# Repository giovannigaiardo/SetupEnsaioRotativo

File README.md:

# SetupEnsaioRotativo
Automação processo de ensaio rotativo para laboratório de plugs e tomadas.

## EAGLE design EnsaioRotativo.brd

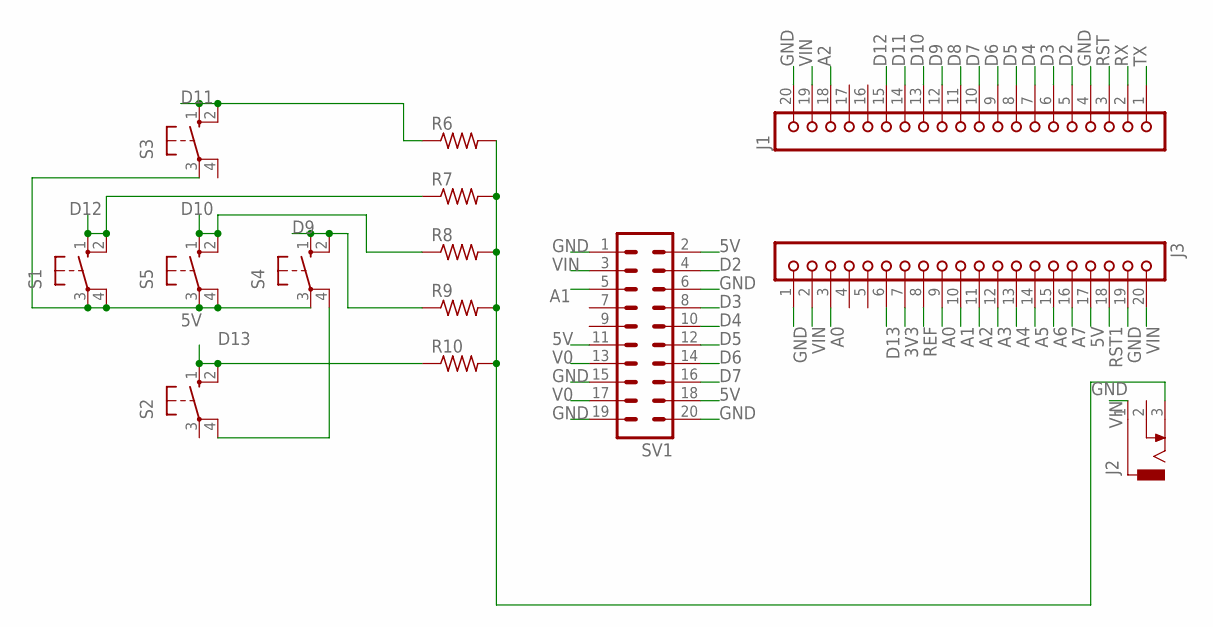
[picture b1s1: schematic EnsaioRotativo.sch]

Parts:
J1, J3: JBK20
J2: DCJ0303
R6, R7, R8, R9, R10: R-US_0207/10; 0207/10
S1, S2, S3, S4, S5: 10-XX; B3F-10XX
SV1: MA10-2

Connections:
3V3: J3.7
5V: J3.17, S1.3, S1.4 (P1), S3.3, S4.3, S5.3, S5.4 (P1), SV1.2, SV1.11, SV1.18
A0: J3.3, J3.9
A1: J3.10, SV1.5
A2: J1.18, J3.11
A3: J3.12
A4: J3.13
A5: J3.14
A6: J3.15
A7: J3.16
D2: J1.5, SV1.4
D3: J1.6, SV1.8
D4: J1.7, SV1.10
D5: J1.8, SV1.12
D6: J1.9, SV1.14
D7: J1.10, SV1.16
D8: J1.11
D9: J1.12, R9.1, S4.1 (S), S4.2 (S1)
D10: J1.13, R8.1, S5.1 (S), S5.2 (S1)
D11: J1.14, R6.1, S3.1 (S), S3.2 (S1)
D12: J1.15, R7.1, S1.1 (S), S1.2 (S1)
D13: J3.6, R10.1, S2.1 (S), S2.2 (S1)
GND: J1.4, J1.20, J2.3, J3.1, J3.19, R6.2, R7.2, R8.2, R9.2, R10.2, SV1.1, SV1.6, SV1.15, SV1.19, SV1.20
unnamed: S2.4 (P1), S4.4 (P1)
REF: J3.8
RST: J1.3
RST1: J3.18
RX: J1.2
TX: J1.1
V0: SV1.13, SV1.17
VIN: J1.19, J2.1, J3.2, J3.20, SV1.3

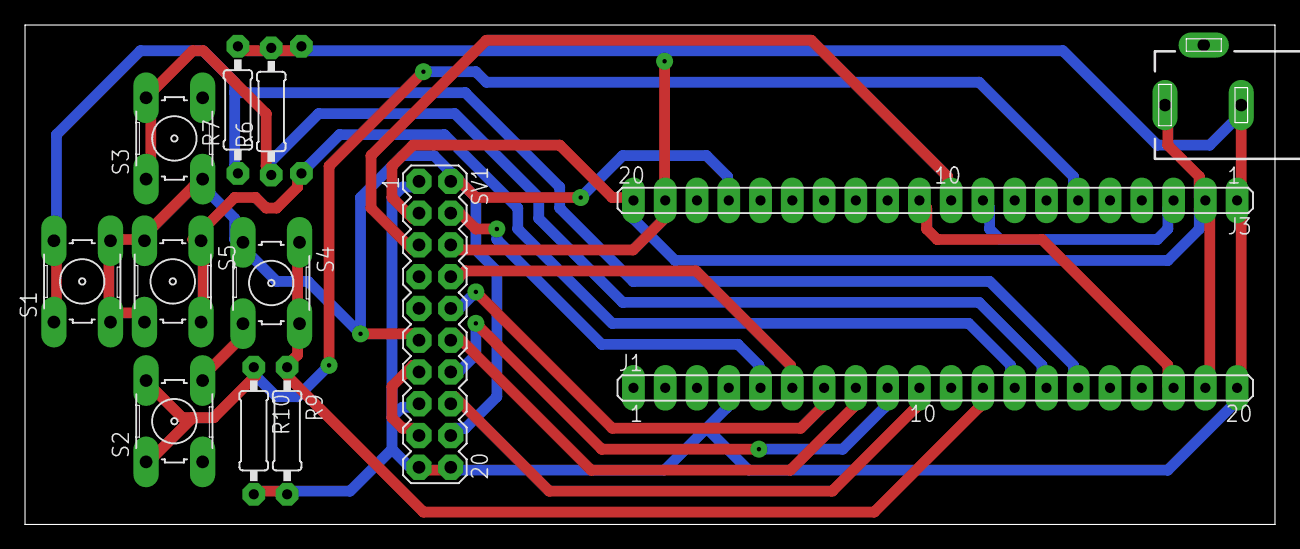
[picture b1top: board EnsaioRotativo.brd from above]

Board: 2 copper layers, 99.9 x 39.9 mm, 14 parts (1 on the bottom side), 19 nets.
